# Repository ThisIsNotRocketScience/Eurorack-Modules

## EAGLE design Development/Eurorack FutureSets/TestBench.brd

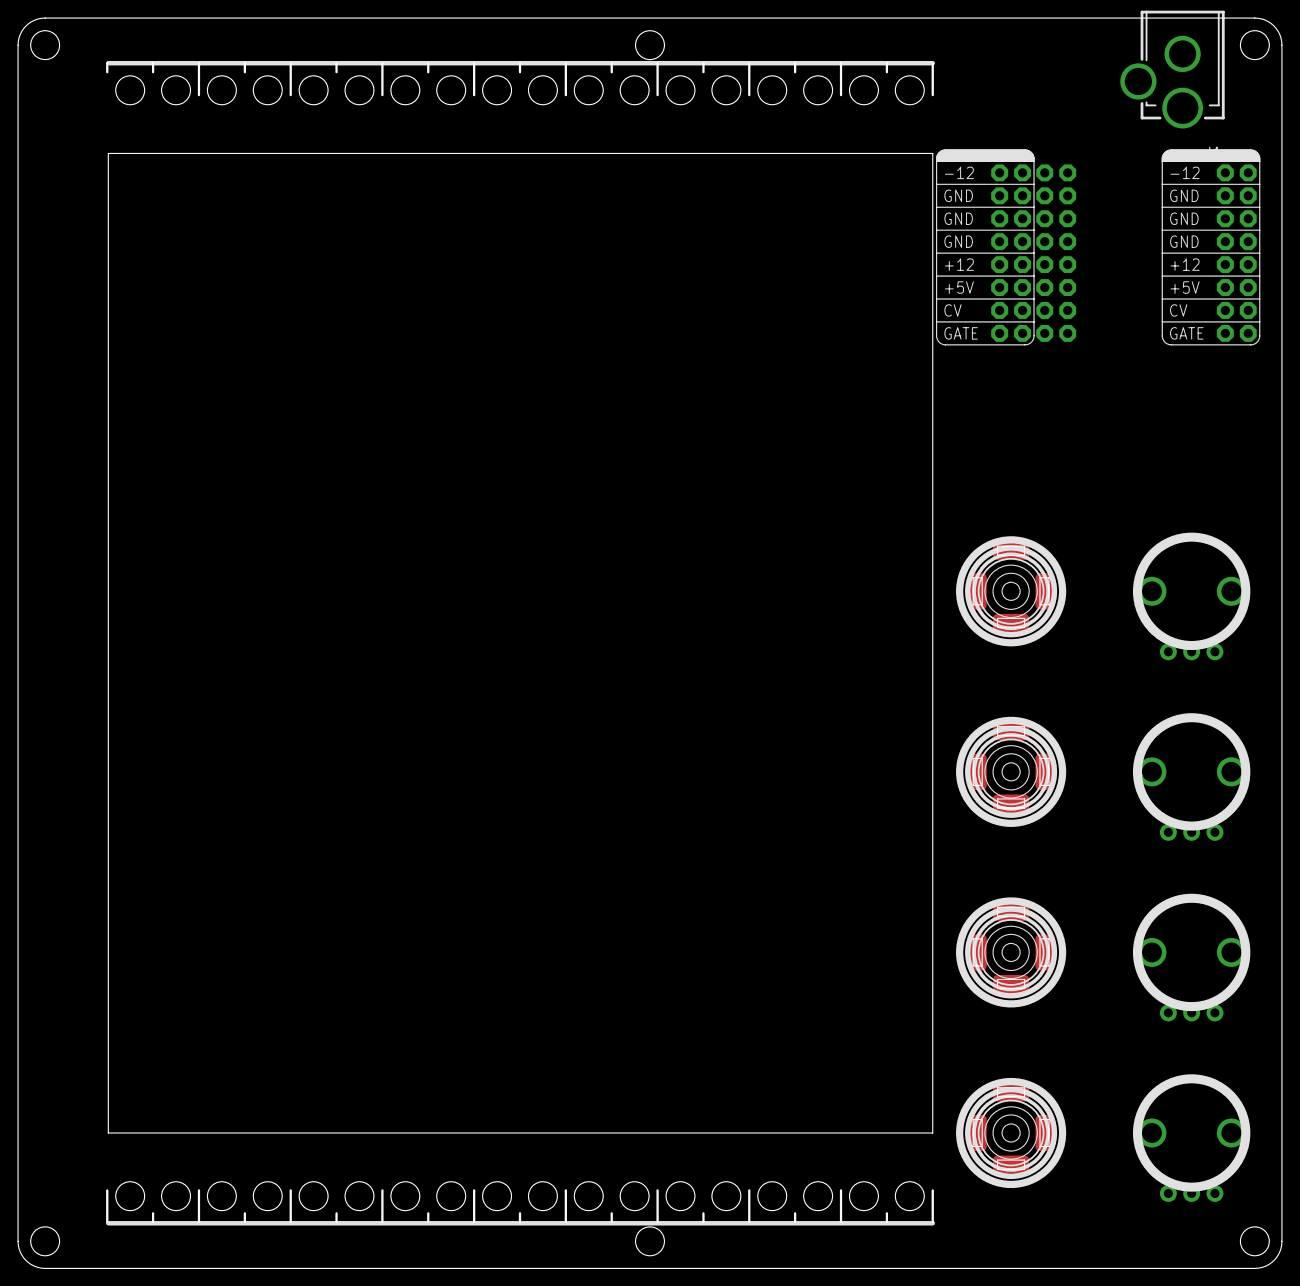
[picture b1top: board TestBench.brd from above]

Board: 2 copper layers, 140.0 x 138.5 mm, 12 parts (1 on the bottom side), 10 nets, no tracks yet.

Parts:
J1: DC_BARREL_JACK_PTH_2MM
U$1, U$2, U$3: POWER; POWER_16
U$4, U$5, U$6, U$7: OG-POTS_ALPS_POT_VERTICAL
U$8, U$9, U$10, U$11: AUDIO-JACKOUTPUT; 3.5MM-JACK-SWITCH-13MM-OUTPUT

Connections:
+5: U$1.11, U$1.12, U$2.11, U$2.12, U$3.11, U$3.12
+12: U$1.9, U$1.10, U$2.9, U$2.10, U$3.9, U$3.10, U$4.P$3, U$5.P$3, U$6.P$3, U$7.P$3
-12: U$1.1, U$1.2, U$2.1, U$2.2, U$3.1, U$3.2, U$4.P$1, U$5.P$1, U$6.P$1, U$7.P$1
CV: U$1.13, U$1.14, U$2.13, U$2.14, U$3.13, U$3.14
GATE: U$1.15, U$1.16, U$2.15, U$2.16, U$3.15, U$3.16
GND: J1.P1, U$1.3, U$1.4, U$1.5, U$1.6, U$1.7, U$1.8, U$2.3, U$2.4, U$2.5, U$2.6, U$2.7, U$2.8, U$3.3, U$3.4, U$3.5, U$3.6, U$3.7, U$3.8, U$8.RING@1, U$8.RING@2, U$9.RING@1, U$9.RING@2, U$10.RING@1, U$10.RING@2, U$11.RING@1, U$11.RING@2
unnamed: U$4.P$2, U$8.SECOND@1, U$8.SECOND@2, U$8.TIP@1, U$8.TIP@2
unnamed: U$5.P$2, U$9.SECOND@1, U$9.SECOND@2, U$9.TIP@1, U$9.TIP@2
unnamed: U$6.P$2, U$10.SECOND@1, U$10.SECOND@2, U$10.TIP@1, U$10.TIP@2
unnamed: U$7.P$2, U$11.SECOND@1, U$11.SECOND@2, U$11.TIP@1, U$11.TIP@2

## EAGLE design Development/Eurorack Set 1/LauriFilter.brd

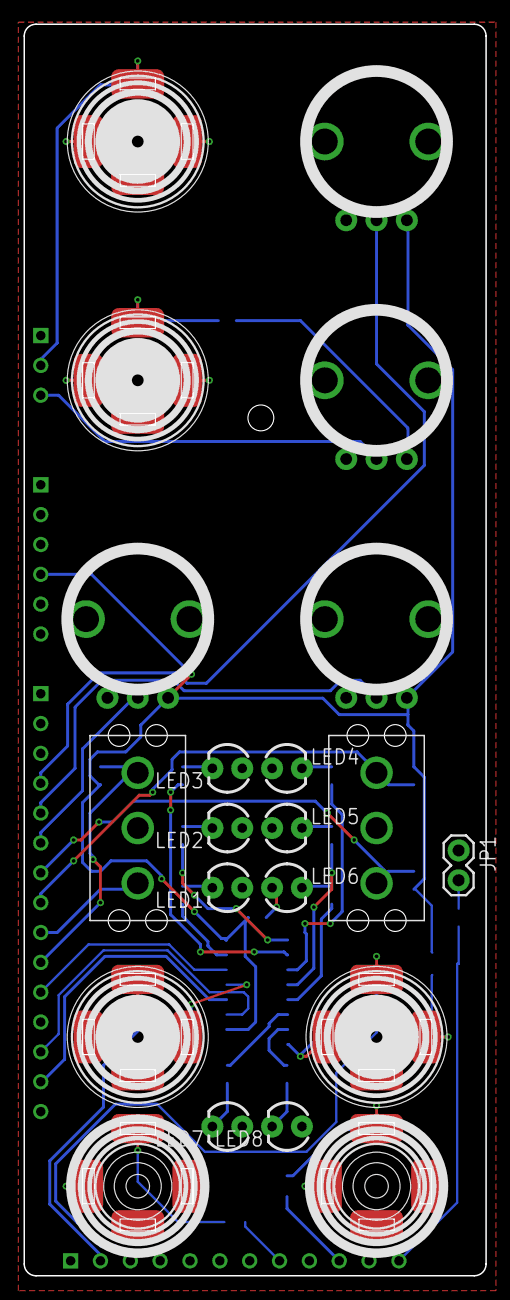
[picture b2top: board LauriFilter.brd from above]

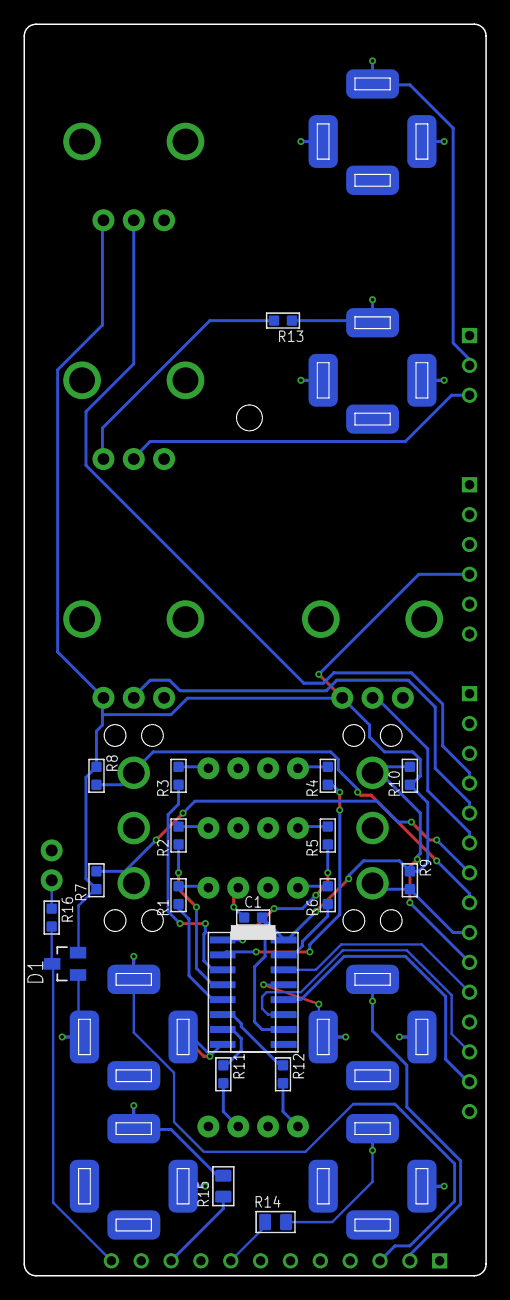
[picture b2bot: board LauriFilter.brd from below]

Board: 2 copper layers, 39.3 x 106.5 mm, 42 parts (19 on the bottom side), 40 nets.

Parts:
C1: 100nF; C0603
D1: BAS70-04; SOT23
IC2: IC_74HC595-SOIC-16; SOIC-16
JP1: M02PTH; 1X02
LED1, LED2, LED3, LED4, LED5, LED6, LED7, LED8: WHITE; LED3MM
R1, R2, R3, R4, R5, R6, R11, R12: 50; R0603
R7, R8, R9, R10: 10k; R0603
R13: 100k; R0603
R14, R15: 300; C0805
R16: 300; R0603
U$1: MCUBOARD; MCUBASEBOARD
U$2: EURORACK_PCB8HP; EURORACK8HPPCB
U$3: CV 1; 3.5MM-JACK-SWITCH-13MM-INPUT
U$4: CV 2; 3.5MM-JACK-SWITCH-13MM-INPUT
U$5: IN 1; 3.5MM-JACK-SWITCH-13MM-INPUT
U$6: IN 2; 3.5MM-JACK-SWITCH-13MM-INPUT
U$7: OUT 1; 3.5MM-JACK-SWITCH-13MM-OUTPUT
U$8: OUT 2; 3.5MM-JACK-SWITCH-13MM-OUTPUT
U$9: CUTOFF; OG-POTS_ALPS_POT_VERTICAL
U$10: RESONANCE; OG-POTS_ALPS_POT_VERTICAL
U$11: DRIVE; OG-POTS_ALPS_POT_VERTICAL
U$12, U$13: ONOFFON; MULTICOMP1MS-ONOFFON
U$14: CV 2; OG-POTS_ALPS_POT_VERTICAL

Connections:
3.3V: C1.2, D1.2, IC2.10, IC2.16, R7.1, R8.1, R9.1, R10.1, U$1.3.3V, U$9.P$3, U$10.P$3, U$11.P$3
CUTOFF: U$1.ADC8, U$9.P$2
DRIVE: U$1.ADC12, U$11.P$2
GND: C1.1, D1.1, IC2.8, IC2.13, JP1.1, LED1.A, LED2.A, LED3.A, LED4.A, LED5.A, LED6.A, LED7.A, LED8.A, U$1.GND@1, U$1.GND@2, U$1.GND@4, U$1.GND@5, U$1.GND@6, U$1.GND@7, U$1.GND@8, U$1.GND@9, U$1.GND_BUS, U$3.RING@1, U$3.RING@2, U$3.SWITCH@1, U$3.SWITCH@2, U$4.RING@1, U$4.RING@2, U$4.SWITCH@1, U$4.SWITCH@2, U$5.RING@1, U$5.RING@2, U$5.SWITCH@1, U$5.SWITCH@2, U$6.RING@1, U$6.RING@2, U$6.SWITCH@1, U$6.SWITCH@2, U$7.RING@1, U$7.RING@2, U$8.RING@1, U$8.RING@2, U$9.P$1, U$10.P$1, U$11.P$1, U$12.2, U$13.2, U$14.P$1
LEDB1: IC2.15, R6.1
LEDB2: IC2.1, R5.1
LEDB3: IC2.2, R4.1
LEDB4: IC2.3, R3.1
LEDB5: IC2.4, R2.1
LEDB6: IC2.5, R1.1
LEDB7: IC2.6, R12.1
LEDB8: IC2.7, R11.1
LEDCLOCK: IC2.11, U$1.TX/D7
LEDDAT: IC2.14, U$1.ADC4
LEDLATCH: IC2.12, U$1.ADC7
MODE1_A: R7.2, U$1.ADC13, U$12.1
MODE1_B: R8.2, U$1.RX/B16, U$12.3
MODE2_A: R9.2, U$1.TX/B17, U$13.1
MODE2_B: R10.2, U$1.ADC14, U$13.3
unnamed: U$1.IN_L, U$5.TIP@1, U$5.TIP@2
unnamed: U$1.IN_R, U$6.TIP@1, U$6.TIP@2
unnamed: U$1.CV_MIX1, U$3.TIP@1, U$3.TIP@2
unnamed: U$1.CV_MIX2, U$14.P$2
unnamed: R14.2, U$7.TIP@1, U$7.TIP@2
unnamed: R15.2, U$8.TIP@1, U$8.TIP@2
unnamed: R13.1, U$4.TIP@1, U$4.TIP@2
unnamed: LED8.K, R11.2
unnamed: LED7.K, R12.2
unnamed: R13.2, U$14.P$3
unnamed: R14.1, U$1.OUT_L
unnamed: R15.1, U$1.OUT_R
unnamed: D1.3, R16.2, U$1.OUT_DAC
unnamed: LED6.K, R1.2
unnamed: LED5.K, R2.2
unnamed: LED4.K, R3.2
unnamed: LED3.K, R4.2
unnamed: LED2.K, R5.2
unnamed: LED1.K, R6.2
unnamed: JP1.2, R16.1
RESONANCE: U$1.ADC9, U$10.P$2

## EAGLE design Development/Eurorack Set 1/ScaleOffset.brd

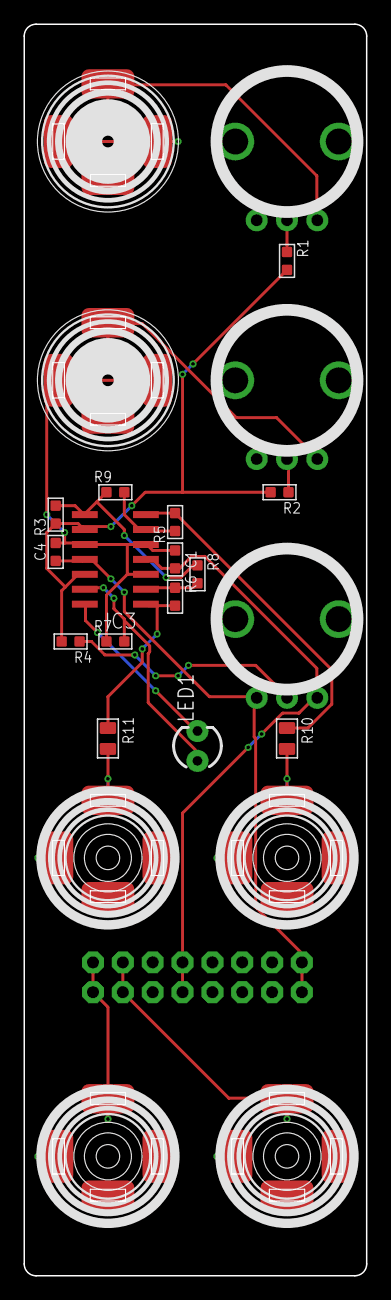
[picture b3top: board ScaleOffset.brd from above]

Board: 2 copper layers, 29.1 x 106.5 mm, 26 parts (1 on the bottom side), 20 nets.

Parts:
C1, C4: 100n; C0603
CV: CV; 3.5MM-JACK-SWITCH-13MM-OUTPUT
GAIN1: Gain 1; OG-POTS_ALPS_POT_VERTICAL
GAIN2: Gain 2; OG-POTS_ALPS_POT_VERTICAL
GATE: GATE; 3.5MM-JACK-SWITCH-13MM-OUTPUT
IC3: TL074D; SO14
IN1: Input 1; 3.5MM-JACK-SWITCH-13MM-INPUT
IN2: Input 2; 3.5MM-JACK-SWITCH-13MM-INPUT
LED1: REDBLUE; LED3MM
OFFSET: Offset; OG-POTS_ALPS_POT_VERTICAL
OUT1: 2; 3.5MM-JACK-SWITCH-13MM-OUTPUT
OUT2: 1; 3.5MM-JACK-SWITCH-13MM-OUTPUT
R1, R2, R3, R4, R8, R9: 100k; R0603
R5, R6: 100K; R0603
R7: 1k; R0603
R10, R11: 51; C0805
U$5: POWER; POWER_16
U$12: EURORACK_PCB6HP; EURORACK6HPPCB

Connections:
12V: C1.2, IC3.4, OFFSET.P$3, U$5.9, U$5.10
-12V: C4.1, IC3.11, OFFSET.P$1, U$5.1, U$5.2
CV: CV.TIP@1, CV.TIP@2, U$5.13, U$5.14
FBOUT1: IC3.7, R5.2, R10.1
FBOUT2: IC3.1, R6.2, R11.1
GATE: GATE.TIP@1, GATE.TIP@2, U$5.15, U$5.16
GND: C1.1, C4.2, CV.RING@1, CV.RING@2, GAIN1.P$1, GAIN2.P$1, GATE.RING@1, GATE.RING@2, IC3.3, IC3.5, IC3.10, IN1.RING@1, IN1.RING@2, IN1.SWITCH@1, IN1.SWITCH@2, IN2.RING@1, IN2.RING@2, IN2.SWITCH@1, IN2.SWITCH@2, OUT1.RING@1, OUT1.RING@2, OUT2.RING@1, OUT2.RING@2, R7.1, U$5.3, U$5.4, U$5.5, U$5.6, U$5.7, U$5.8
unnamed: IC3.6, R5.1, R9.2
unnamed: GAIN2.P$3, IN2.TIP@1, IN2.TIP@2
unnamed: GAIN1.P$3, IN1.TIP@1, IN1.TIP@2
unnamed: GAIN1.P$2, R1.1
unnamed: GAIN2.P$2, R2.1
unnamed: IC3.8, R3.2, R8.1, R9.1
unnamed: IC3.14, LED1.K
unnamed: IC3.13, LED1.A, R7.2
unnamed: IC3.2, R6.1, R8.2
OFFSET: OFFSET.P$2, R4.1
OUT1: OUT1.TIP@1, OUT1.TIP@2, R10.2
OUT2: OUT2.TIP@1, OUT2.TIP@2, R11.2
SUMMING: IC3.9, IC3.12, R1.2, R2.2, R3.1, R4.2

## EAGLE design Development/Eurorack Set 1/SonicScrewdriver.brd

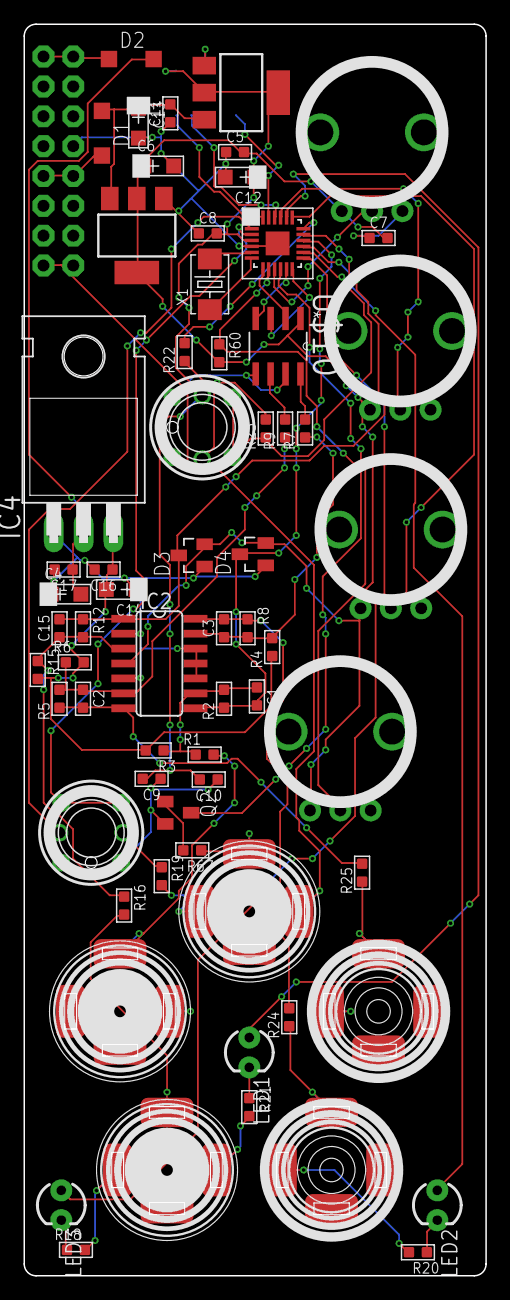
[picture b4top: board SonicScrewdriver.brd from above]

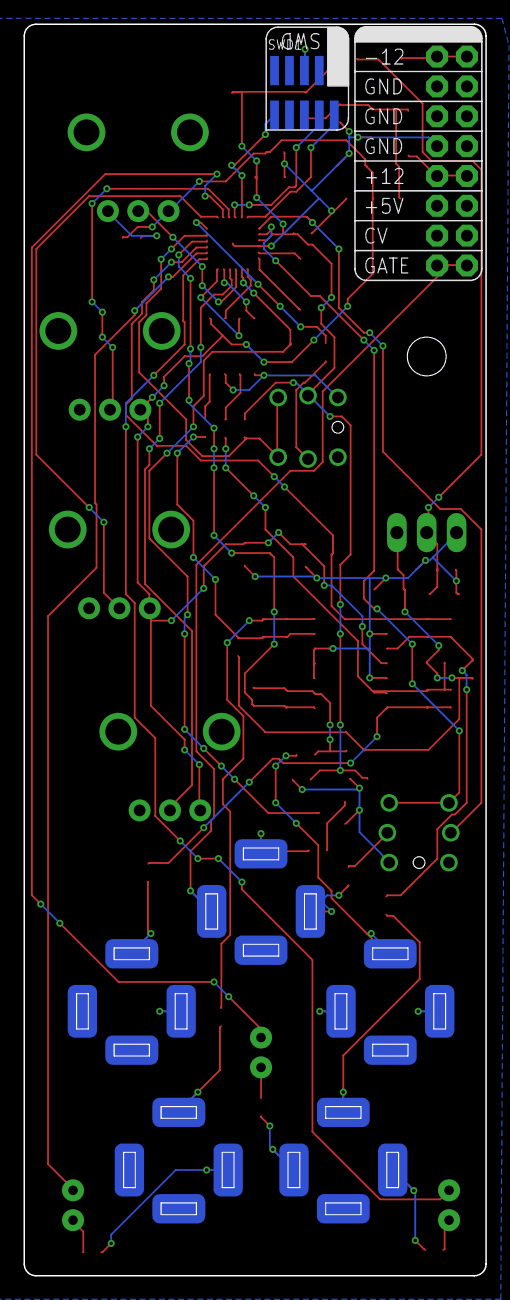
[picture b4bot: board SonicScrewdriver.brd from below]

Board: 2 copper layers, 39.3 x 106.5 mm, 68 parts (2 on the bottom side), 50 nets.

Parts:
C1, C2, C3, C15: 3.3n; C0603
C4, C6, C12, C14: 10uF; AVX-A
C5, C7, C8, C10, C16, C17: 100nF; C0603
C9: 1uF; C0603
C11: 100Nf; C0603
C13: 10Uf; AVX-A
D1, D2: 1N5819HW; SOD123
D3, D4: BAS70-04; SOT23
GATE: Gate; 3.5MM-JACK-SWITCH-13MM-INPUT
IC1, IC3: LD1117AS33TR; SOT223
IC2: MCP6004; SO14
IC4: 7905; TO220H
IN1: In 2; 3.5MM-JACK-SWITCH-13MM-INPUT
IN2: In 1; 3.5MM-JACK-SWITCH-13MM-INPUT
LED1, LED2, LED3: LED3MM
Q2: MMBT3904; SOT23-BEC
R1, R3, R15, R16, R67: 100k; R0603
R2, R12: 33k; R0603
R4, R6: 6.6k; R0603
R5, R8: 20k; R0603
R7, R9: 3.3k; R0603
R13: A; OG-POTS_ALPS_POT_VERTICAL
R14: D; OG-POTS_ALPS_POT_VERTICAL
R17: B; OG-POTS_ALPS_POT_VERTICAL
R18, R19, R20, R21, R22, R23: 120; R0603
R24, R25: 51; R0603
R60: 10k; R0603
R90: C; OG-POTS_ALPS_POT_VERTICAL
SWD1: CORTEX_SWD; M50-3600542
U1: MKL02Z32VFK4; QFN50P400X400X100-25N
U$1: POWER; POWER_16
U$2: EURORACK_PCB8HP; EURORACK8HPPCB
U$3, U$6: SWITCH_W_LED_PB6149L-X-102WHITE; PB6149L
U$7: Out 2; 3.5MM-JACK-SWITCH-13MM-OUTPUT
U$8: Out 1; 3.5MM-JACK-SWITCH-13MM-OUTPUT
U$10: MCP4822-E/SN; SOIC8-N_MC
X1: CRYSTAL-0500290P1; 2P-SMD-5.0X3.2

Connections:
3.3V: C8.2, C9.2, C10.2, C12.+, IC1.2, IC1.4, R23.2, SWD1.1, U1.3, U$3.LEDPOS
3.3V_A: C5.2, C6.+, C7.2, D3.2, D4.2, IC2.4, IC3.2, IC3.4, R13.P$1, R14.P$1, R17.P$1, R60.2, R90.P$1, U$10.1
ADC_1: C15.2, D3.3, IC2.1, R12.1, U1.15
ADC_2: C1.2, D4.3, IC2.8, R2.1, U1.16
DACCS: U1.7, U$10.2
DACSCK: U1.12, U$10.3
DACSDI: U1.11, U$10.4
GATE: Q2.C, R60.1, U1.8
GND: C4.+, C5.1, C6.-, C7.1, C8.1, C9.1, C10.1, C11.1, C12.-, C13.-, C14.+, C16.2, C17.2, D3.1, D4.1, GATE.RING@1, GATE.RING@2, IC1.1, IC2.2, IC2.5, IC2.10, IC2.11, IC2.12, IC3.1, IC4.1, IN1.RING@1, IN1.RING@2, IN1.SWITCH@1, IN1.SWITCH@2, IN2.RING@1, IN2.RING@2, IN2.SWITCH@1, IN2.SWITCH@2, Q2.E, R13.P$3, R14.P$3, R17.P$3, R18.2, R19.2, R20.2, R21.2, R90.P$3, SWD1.3, SWD1.5, U1.4, U1.25, U$1.3, U$1.4, U$1.5, U$1.6, U$1.7, U$1.8, U$3.3, U$3.4, U$6.3, U$6.4, U$7.RING@1, U$7.RING@2, U$8.RING@1, U$8.RING@2, U$10.5, U$10.7
KNOB_A: R90.P$2, U1.19
KNOB_B: R13.P$2, U1.9
KNOB_C: R14.P$2, U1.10
KNOB_D: R17.P$2, U1.21
LED1: U1.1, U$6.LEDPOS
LED2: LED1.A, U1.20
LED3: LED2.A, U1.14
LED4: LED3.A, U1.13
unnamed: U1.5, X1.2
unnamed: U1.6, X1.1
unnamed: IN1.TIP@1, IN1.TIP@2, R16.2
unnamed: C15.1, IC2.3, R12.2, R15.1, R16.1
unnamed: SWD1.4, U1.22
unnamed: IN2.TIP@1, IN2.TIP@2, R1.2
unnamed: SWD1.2, U1.24
unnamed: C1.1, IC2.9, R1.1, R2.2, R3.1
unnamed: C2.1, IC2.6, R5.2, R6.1, R9.1
unnamed: C3.1, IC2.13, R4.2, R7.1, R8.2
unnamed: R7.2, U$10.8
unnamed: R9.2, U$10.6
unnamed: D1.A, U$1.9, U$1.10
unnamed: R19.1, U$6.LEDNEG
unnamed: LED3.K, R18.1
unnamed: LED2.K, R20.1
unnamed: LED1.K, R21.1
unnamed: C3.2, IC2.14, R8.1, R24.2
unnamed: R22.1, U$3.LEDNEG
unnamed: R25.1, U$8.TIP@1, U$8.TIP@2
unnamed: R24.1, U$7.TIP@1, U$7.TIP@2
unnamed: C2.2, IC2.7, R5.1, R25.2
unnamed: GATE.TIP@1, GATE.TIP@2, R67.1
unnamed: D2.C, U$1.1, U$1.2
unnamed: Q2.B, R67.2
PTA1: SWD1.10, U1.23
RACK_GATE: GATE.SWITCH@1, GATE.SWITCH@2, U$1.15, U$1.16
REF_-5V: C14.-, C16.1, IC4.3, R3.2, R4.1, R6.2, R15.2
SW1: U1.2, U$6.1, U$6.2
SW2: R23.1, U1.17, U$3.1, U$3.2
SW2LED: R22.2, U1.18
VEE: C4.-, C17.1, D2.A, IC4.2
VIN: C11.2, C13.+, D1.C, IC1.3, IC3.3

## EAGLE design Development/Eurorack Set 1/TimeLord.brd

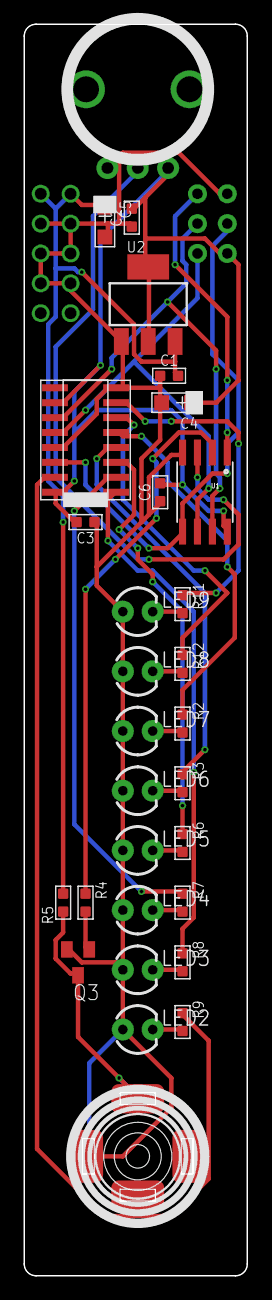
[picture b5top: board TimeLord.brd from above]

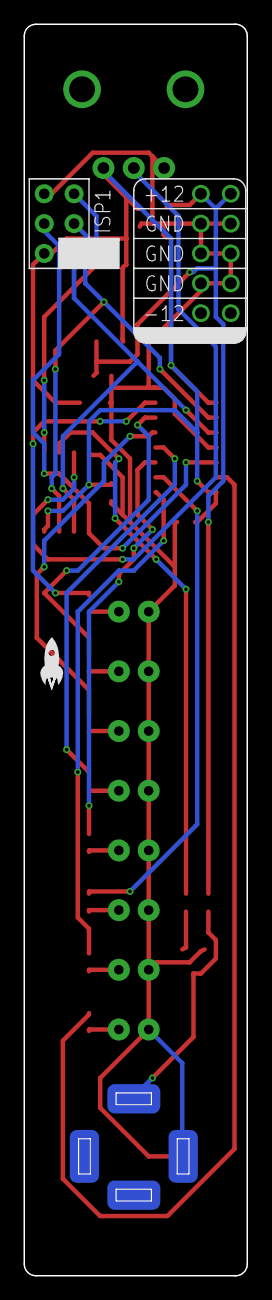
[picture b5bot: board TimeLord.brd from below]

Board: 2 copper layers, 19.0 x 106.5 mm, 34 parts (3 on the bottom side), 27 nets.

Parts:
C1, C2, C3, C6: 100nF; C0603
C4, C5: 10uF; AVX-A
IC2: IC_74HC595-SOIC-16; SOIC-16
ISP1: AVRISP-6; AVRISP
LED2, LED3, LED4, LED5, LED6, LED7, LED8, LED9: WHITE; LED3MM
Q3: MMBT3904; SOT23-BEC
R2, R3, R6, R7, R8, R9, R11, R12: 50; R0603
R4: 100k; R0603
R5: 10k; R0603
U1: Tiny85-20-SMT; SO08-EIAJ
U2: CJ1117-5.0-1310170P1; SOT223
U$1: POWER_SIMPLE10-OTHERSIDE; POWER_10_LABELSOTHERSIDE
U$2: EURORACK_PCB4HP; EURORACK4HPPCB
U$3: CLOCK; 3.5MM-JACK-SWITCH-13MM-OUTPUT
U$4: SPEED; OG-POTS_ALPS_POT_VERTICAL
U$5: JUSTATINYROCKET

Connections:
5V: C2.2, C3.2, C4.+, C6.2, IC2.10, IC2.16, ISP1.2, U1.8, U2.2, U2.TER, U$4.P$3
12V: C1.2, C5.+, R5.2, U2.3, U$1.9, U$1.10
CLOCKJACK: Q3.C, R5.1, U$3.TIP@1, U$3.TIP@2
CLOCKOUT: R4.1, U1.2
CLOCKPOT: U1.3, U$4.P$2
GND: C1.1, C2.1, C3.1, C4.-, C5.-, C6.1, IC2.8, IC2.13, ISP1.6, LED2.A, LED3.A, LED4.A, LED5.A, LED6.A, LED7.A, LED8.A, LED9.A, Q3.E, U1.4, U2.1, U$1.3, U$1.4, U$1.5, U$1.6, U$1.7, U$1.8, U$3.RING@1, U$3.RING@2, U$4.P$1
LEDB1: IC2.15, R9.1
LEDB2: IC2.1, R8.1
LEDB3: IC2.2, R7.1
LEDB4: IC2.3, R6.1
LEDB5: IC2.4, R3.1
LEDB6: IC2.5, R2.1
LEDB7: IC2.6, R12.1
LEDB8: IC2.7, R11.1
LEDCLOCK: IC2.11, ISP1.3, U1.7
LEDDAT: IC2.14, ISP1.4, U1.5
LEDLATCH: IC2.12, ISP1.1, U1.6
unnamed: LED8.K, R12.2
unnamed: LED9.K, R11.2
unnamed: Q3.B, R4.2
unnamed: LED7.K, R2.2
unnamed: LED6.K, R3.2
unnamed: LED5.K, R6.2
unnamed: LED4.K, R7.2
unnamed: LED3.K, R8.2
unnamed: LED2.K, R9.2
RESET: ISP1.5, U1.1

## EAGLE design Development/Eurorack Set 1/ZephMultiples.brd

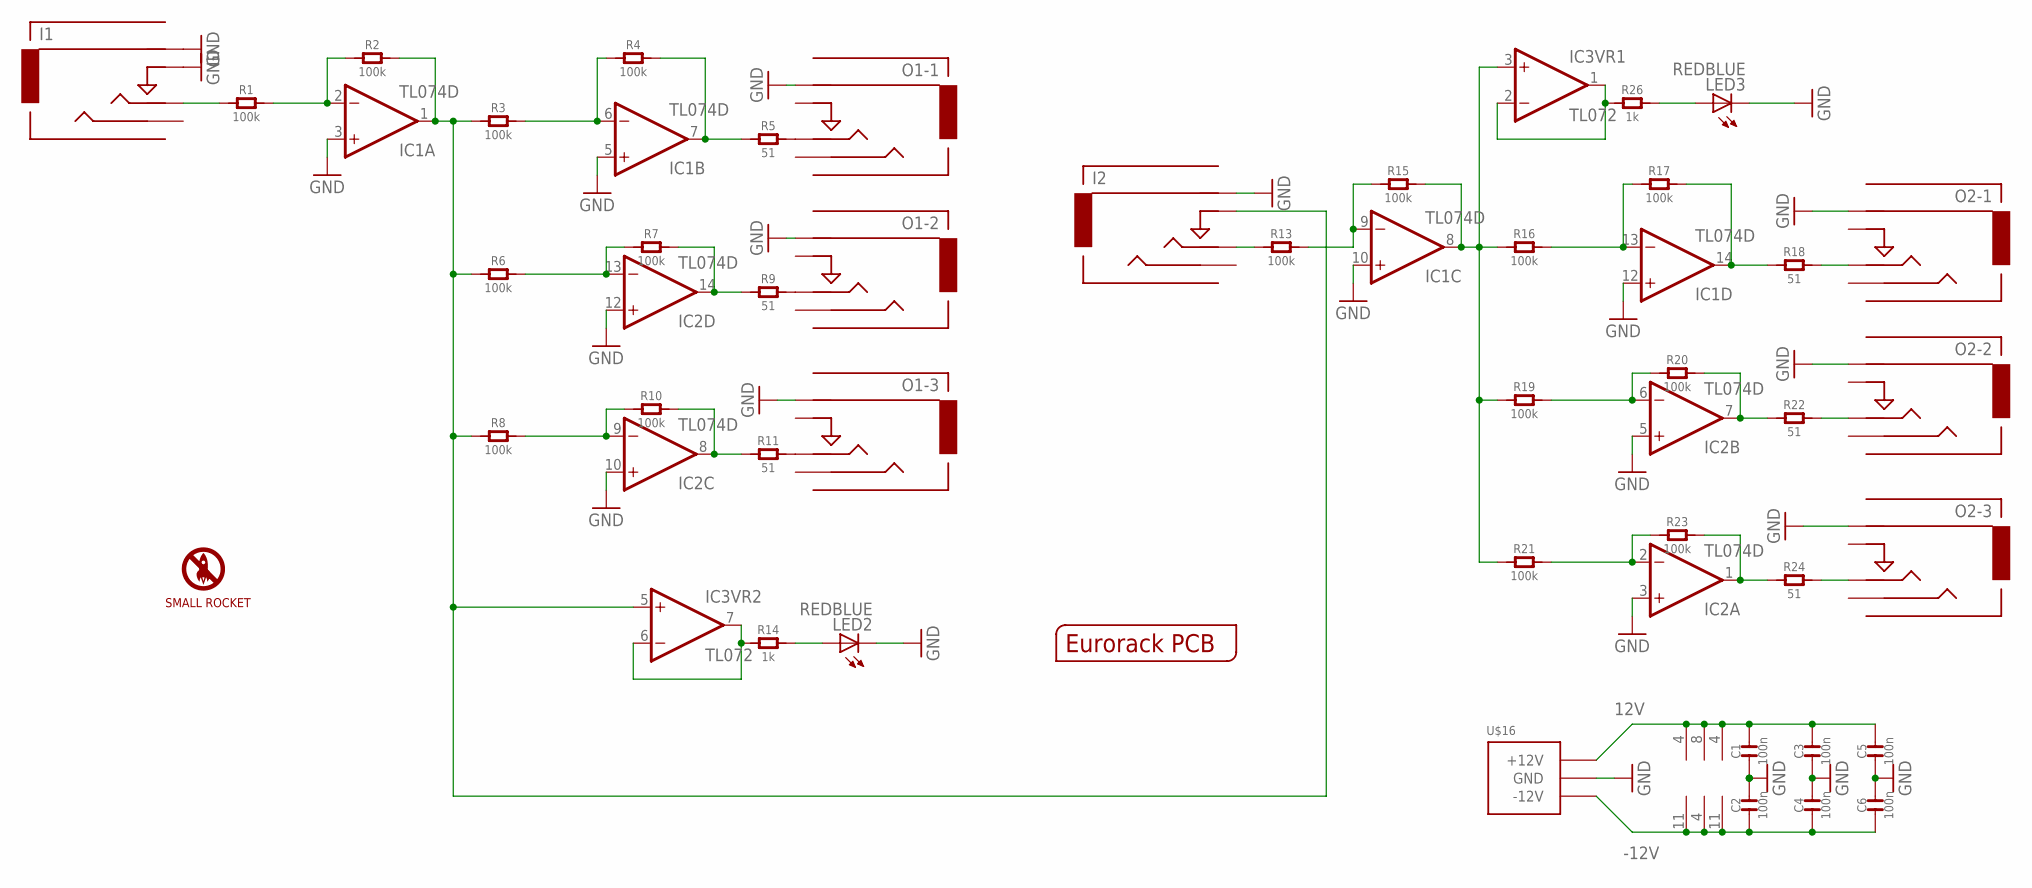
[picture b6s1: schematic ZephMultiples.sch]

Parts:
C1, C2, C3, C4, C5, C6: 100n; C0603
I1: In 1; 3.5MM-JACK-SWITCH-13MM-INPUT
I2: In 2; 3.5MM-JACK-SWITCH-13MM-INPUT
IC1, IC2: TL074D; SO14
IC3: TL072; SO08
LED2, LED3: REDBLUE; LED3MM
O1-1, O1-2, O1-3, O2-1, O2-2, O2-3: AUDIO-JACKOUTPUT; 3.5MM-JACK-SWITCH-13MM-OUTPUT
R1, R2, R3, R4, R6, R7, R8, R10, R13, R15, R16, R17, R19, R20, R21, R23: 100k; R0603
R5, R9, R11, R18, R22, R24: 51; R0603
R14, R26: 1k; R0603
U$1: SMALLROCKET
U$15: EURORACK_PCB4HP; EURORACK4HPPCB
U$16: POWER_SIMPLE10-OTHERSIDE; POWER_10_LABELSOTHERSIDE

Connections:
12V: C1.2, C3.2, C5.2, IC1.4 (V+), IC2.4 (V+), IC3.8 (V+), U$16.9 (+12V), U$16.10 (+12V)
-12V: C2.1, C4.1, C6.1, IC1.11 (V-), IC2.11 (V-), IC3.4 (V-), U$16.1 (-12V), U$16.2 (-12V)
GND: C1.1, C2.2, C3.1, C4.2, C5.1, C6.2, I1.RING@1 (RING), I1.RING@2 (RING), I1.SWITCH@1 (SWITCH), I1.SWITCH@2 (SWITCH), I2.RING@1 (RING), I2.RING@2 (RING), IC1.3 (+IN), IC1.5 (+IN), IC1.10 (+IN), IC1.12 (+IN), IC2.3 (+IN), IC2.5 (+IN), IC2.10 (+IN), IC2.12 (+IN), LED2.K (C), LED3.K (C), O1-1.RING@1 (RING), O1-1.RING@2 (RING), O1-2.RING@1 (RING), O1-2.RING@2 (RING), O1-3.RING@1 (RING), O1-3.RING@2 (RING), O2-1.RING@1 (RING), O2-1.RING@2 (RING), O2-2.RING@1 (RING), O2-2.RING@2 (RING), O2-3.RING@1 (RING), O2-3.RING@2 (RING), U$16.3 (GND), U$16.4 (GND), U$16.5 (GND), U$16.6 (GND), U$16.7 (GND), U$16.8 (GND)
LED2DRIVE: IC3.6 (-IN), IC3.7 (OUT), R14.1
LED3DRIVE: IC3.1 (OUT), IC3.2 (-IN), R26.1
unnamed: I1.TIP@1 (TIP), I1.TIP@2 (TIP), R1.1
unnamed: IC1.2 (-IN), R1.2, R2.1
unnamed: I2.SWITCH@1 (SWITCH), I2.SWITCH@2 (SWITCH), IC1.1 (OUT), IC3.5 (+IN), R2.2, R3.1, R6.1, R8.1
unnamed: IC1.6 (-IN), R3.2, R4.1
unnamed: IC1.7 (OUT), R4.2, R5.1
unnamed: IC2.13 (-IN), R6.2, R7.1
unnamed: IC2.9 (-IN), R8.2, R10.1
unnamed: IC2.14 (OUT), R7.2, R9.1
unnamed: IC2.8 (OUT), R10.2, R11.1
unnamed: O1-1.TIP@1 (TIP), O1-1.TIP@2 (TIP), R5.2
unnamed: O1-2.TIP@1 (TIP), O1-2.TIP@2 (TIP), R9.2
unnamed: O1-3.TIP@1 (TIP), O1-3.TIP@2 (TIP), R11.2
unnamed: I2.TIP@1 (TIP), I2.TIP@2 (TIP), R13.1
unnamed: IC1.9 (-IN), R13.2, R15.1
unnamed: IC1.8 (OUT), IC3.3 (+IN), R15.2, R16.1, R19.1, R21.1
unnamed: IC1.13 (-IN), R16.2, R17.1
unnamed: IC1.14 (OUT), R17.2, R18.1
unnamed: IC2.6 (-IN), R19.2, R20.1
unnamed: IC2.2 (-IN), R21.2, R23.1
unnamed: IC2.7 (OUT), R20.2, R22.1
unnamed: IC2.1 (OUT), R23.2, R24.1
unnamed: O2-1.TIP@1 (TIP), O2-1.TIP@2 (TIP), R18.2
unnamed: O2-2.TIP@1 (TIP), O2-2.TIP@2 (TIP), R22.2
unnamed: O2-3.TIP@1 (TIP), O2-3.TIP@2 (TIP), R24.2
unnamed: LED2.A, R14.2
unnamed: LED3.A, R26.2

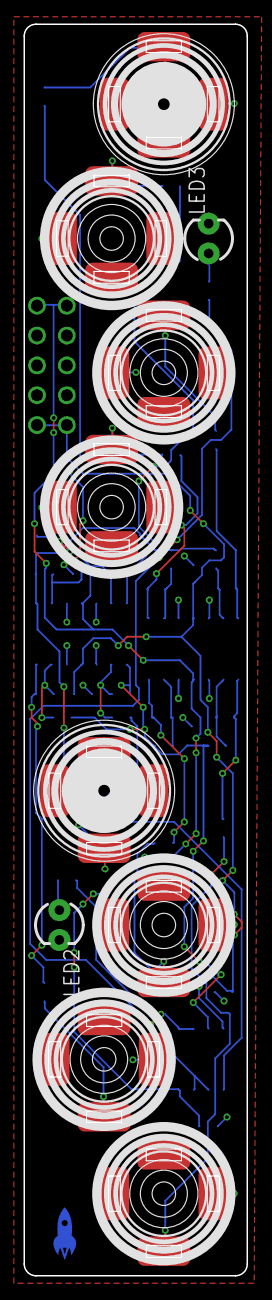
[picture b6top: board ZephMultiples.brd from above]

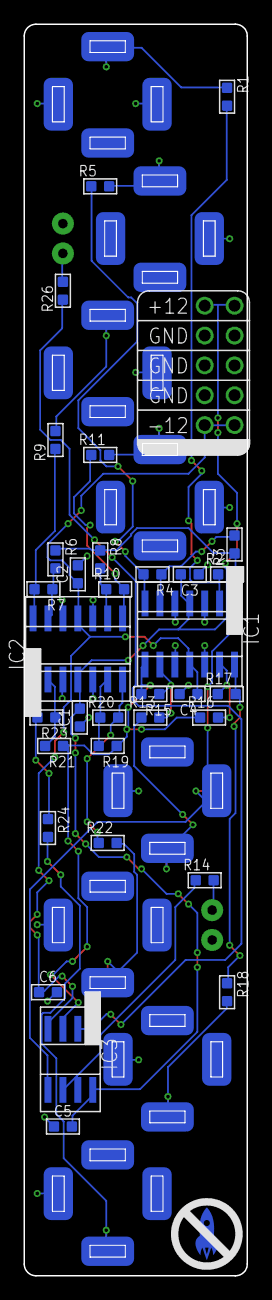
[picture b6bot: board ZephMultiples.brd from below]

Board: 2 copper layers, 19.0 x 106.5 mm, 46 parts (35 on the bottom side), 31 nets.

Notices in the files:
parts and their libraries:
SparkFun-LED: Licensing: CC v3.0 Share-Alike You are welcome to use this library for commercial purposes.
